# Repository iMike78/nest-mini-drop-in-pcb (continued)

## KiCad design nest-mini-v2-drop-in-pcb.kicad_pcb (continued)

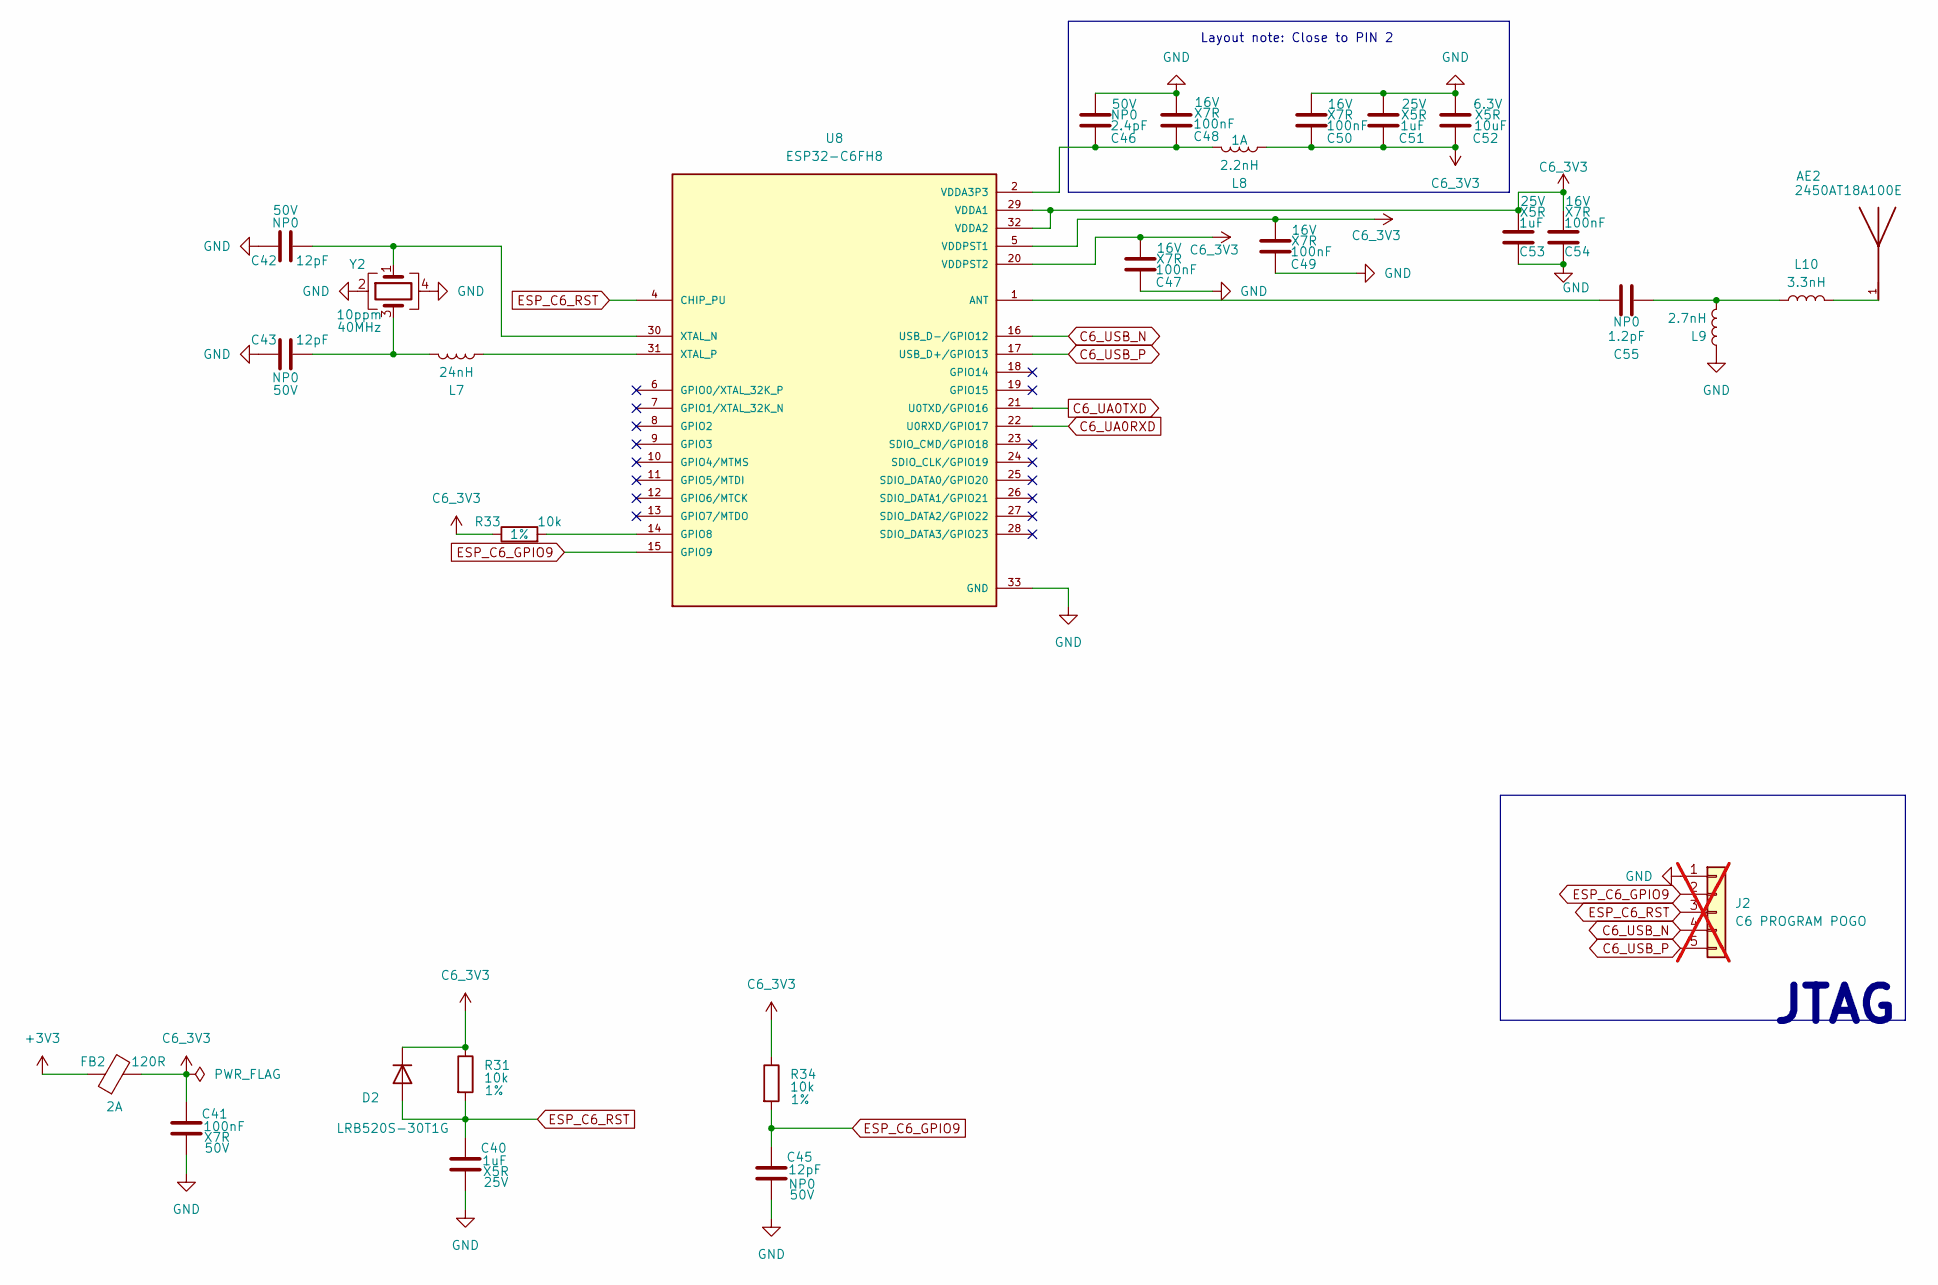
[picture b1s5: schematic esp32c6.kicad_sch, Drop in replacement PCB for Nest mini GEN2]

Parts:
AE2: 2450AT18A100E; Johanson_2450AT18x100; PARTREV 1.3; LCSC Part # C89334
C40, C51, C53: 1uF; C_0402_1005Metric; Voltage 25V; Manufacturer Part CL05A105KA5NQNC; LCSC Part # C52923
C41: 100nF; C_0603_1608Metric; Voltage 50V; Manufacturer Part CC0603KRX7R9BB104; LCSC Part # C14663
C42, C43, C45: 12pF; C_0402_1005Metric; Voltage 50V; Manufacturer Part 0402CG120J500NT; LCSC Part # C1547
C46: 2.4pF; C_0402_1005Metric; Voltage 50V; Manufacturer Part 0402CG2R4C500NT; LCSC Part # C48346
C47, C48, C49, C50, C54: 100nF; C_0402_1005Metric; Voltage 16V; Manufacturer Part CL05B104KO5NNNC; LCSC Part # C1525
C52: 10uF; C_0402_1005Metric; Voltage 6.3V; Manufacturer Part CL05A106MQ5NUNC; LCSC Part # C15525
C55: 1.2pF; C_0402_1005Metric; Voltage 50V; Manufacturer Part CC0402BRNPO9BN1R2; LCSC Part # C327292
D2: LRB520S-30T1G; D_SOD-523; Manufacturer Part LRB520S-30T1G; LCSC Part # C83680
FB2: 120R; BLM18PG121SN1D; Part number BLM18PG121SN1D; LCSC Part # C14709
J2: C6 PROGRAM POGO; PinHeader_1x05_P2.54mm_Vertical; not fitted
L7: 24nH; L_0402_1005Metric; Manufacturer Part LQW15AN24NJ00D; LCSC Part # C341784
L8: 2.2nH; L_0402_1005Metric; Manufacturer Part LQG15HS2N2B02D; LCSC Part # C162540
L9: 2.7nH; L_0402_1005Metric; Manufacturer Part MHQ1005P2N7BT000; LCSC Part # C434826
L10: 3.3nH; L_0402_1005Metric; Manufacturer Part SDCL1005C3N3STDF; LCSC Part # C16526
R31, R33, R34: 10k; R_0402_1005Metric; Tolerance 1%; Manufacturer Part 0402WGF1002TCE; LCSC Part # C25744
U8: ESP32-C6FH8; ESP32-C6FH4; Manufacturer Part ESP32-C6FH8
Y2: 40MHz; Crystal_SMD_2016-4Pin_2.0x1.6mm; Tolerance 10ppm; Manufacturer Part XRCGB40M000F1S1BR0; LCSC Part # C1870451

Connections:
+3V3: FB2.1; also elsewhere on the board
C6_3V3: C41.1, C47.2, C49.2, C50.1, C51.1, C52.1, C53.2, C54.2, D2.1 (K), FB2.2, L8.2, R31.1, R33.1, R34.1, U8.5 (VDDPST1), U8.20 (VDDPST2), U8.29 (VDDA1), U8.32 (VDDA2)
C6_UA0RXD: U8.22 (U0RXD/GPIO17); also elsewhere on the board
C6_UA0TXD: U8.21 (U0TXD/GPIO16); also elsewhere on the board
C6_USB_N: J2.4, U8.16 (USB_D-/GPIO12)
C6_USB_P: J2.5, U8.17 (USB_D+/GPIO13)
ESP_C6_GPIO9: C45.1, J2.2, R34.2, U8.15 (GPIO9); also elsewhere on the board
ESP_C6_RST: C40.1, D2.2 (A), J2.3, R31.2, U8.4 (CHIP_PU); also elsewhere on the board
GND: C40.2, C41.2, C42.1, C43.1, C45.2, C46.2, C47.1, C48.2, C49.1, C50.2, C51.2, C52.2, C53.1, C54.1, J2.1, L9.1, U8.33 (GND), Y2.2, Y2.4; also elsewhere on the board
unnamed: AE2.1, L10.2
unnamed: C43.2, L7.2, Y2.3
unnamed: C55.1, L9.2, L10.1
unnamed: C55.2, U8.1 (ANT)
unnamed: R33.2, U8.14 (GPIO8)
unnamed: C42.2, U8.30 (XTAL_N), Y2.1
unnamed: L7.1, U8.31 (XTAL_P)
VDDA3P3: C46.1, C48.1, L8.1, U8.2 (VDDA3P3), U8.3 (VDDA3P3)

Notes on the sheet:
Layout note: Close to PIN 2
JTAG

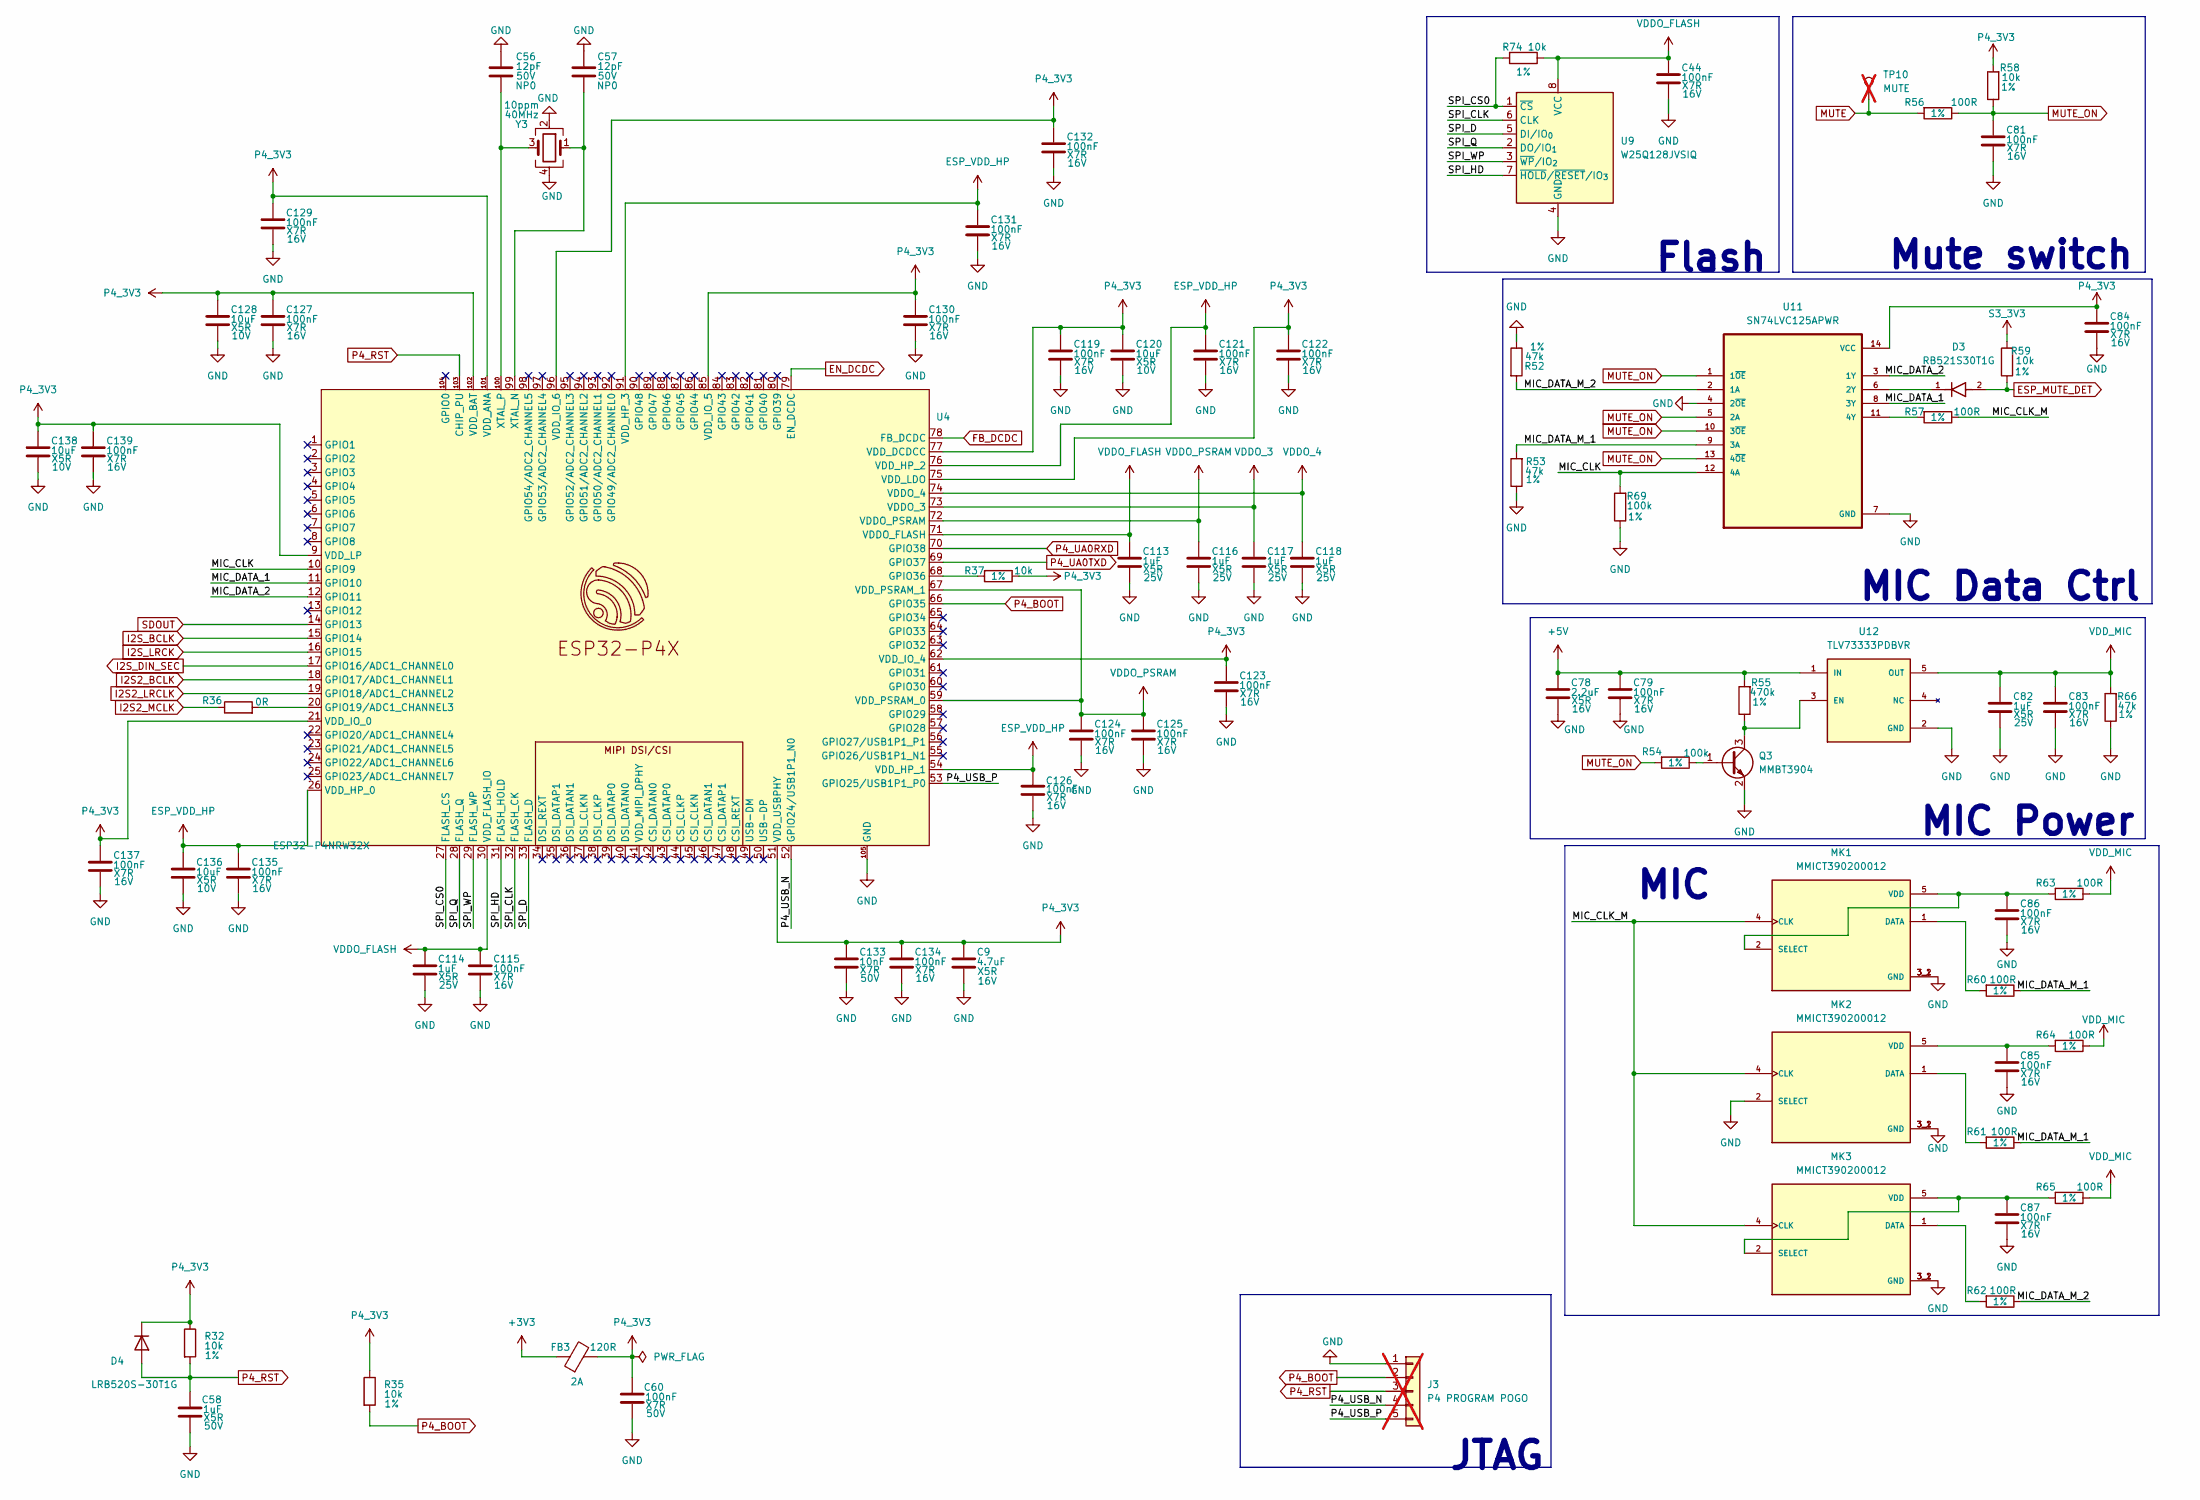
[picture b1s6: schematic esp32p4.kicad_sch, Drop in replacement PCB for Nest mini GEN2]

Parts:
C9: 4.7uF; C_0603_1608Metric; Voltage 16V; Manufacturer Part CL10A475KO8NNNC; LCSC Part # C19666
C44, C79, C81, C83, C84, C85, C86, C87, C115, C119, C121, C122, C123, C124, C125, C126, C127, C129, C130, C131, C132, C134, C135, C137, C139: 100nF; C_0402_1005Metric; Voltage 16V; Manufacturer Part CL05B104KO5NNNC; LCSC Part # C1525
C56, C57: 12pF; C_0402_1005Metric; Voltage 50V; Manufacturer Part 0402CG120J500NT; LCSC Part # C1547
C58: 1uF; C_0603_1608Metric; Voltage 50V; Manufacturer Part CL10A105KB8NNNC; LCSC Part # C15849
C60: 100nF; C_0603_1608Metric; Voltage 50V; Manufacturer Part CC0603KRX7R9BB104; LCSC Part # C14663
C78: 2.2uF; C_0603_1608Metric; Voltage 16V; Manufacturer Part CL10A225KO8NNNC; LCSC Part # C23630
C82, C113, C114, C116, C117, C118: 1uF; C_0402_1005Metric; Voltage 25V; Manufacturer Part CL05A105KA5NQNC; LCSC Part # C52923
C120, C128, C136, C138: 10uF; C_0603_1608Metric; Voltage 10V; Manufacturer Part CL10A106KP8NNNC; LCSC Part # C19702
C133: 10nF; C_0402_1005Metric; Voltage 50V; Manufacturer Part CL05B103KB5NNNC; LCSC Part # C15195
D3: RB521S30T1G; DIOM168X70N; PARTREV 7/11/1905; LCSC Part # C27636108
D4: LRB520S-30T1G; D_SOD-523; Manufacturer Part LRB520S-30T1G; LCSC Part # C83680
FB3: 120R; BLM18PG121SN1D; Part number BLM18PG121SN1D; LCSC Part # C14709
J3: P4 PROGRAM POGO; PinHeader_1x05_P2.54mm_Vertical; not fitted
MK1, MK2, MK3: MMICT390200012; MIC_T3902; PARTREV 1.0; LCSC Part # C3171752
Q3: MMBT3904; SOT-23; Manufacturer Part MMBT3904; LCSC Part # C20526
R32, R35, R37, R58, R59, R74: 10k; R_0402_1005Metric; Tolerance 1%; Manufacturer Part 0402WGF1002TCE; LCSC Part # C25744
R36: 0R; R_0402_1005Metric; Tolerance 5%; Manufacturer Part 0402WGF0000TCE; LCSC Part # C17168
R52, R53, R66: 47k; R_0402_1005Metric; Tolerance 1%; Manufacturer Part 0402WGF4702TCE; LCSC Part # C25792
R54, R69: 100k; R_0402_1005Metric; Tolerance 1%; Manufacturer Part 0402WGF1003TCE; LCSC Part # C25741
R55: 470k; R_0402_1005Metric; Tolerance 1%; Manufacturer Part 0402WGF4703TCE; LCSC Part # C25790
R56, R57, R60, R61, R62, R63, R64, R65: 100R; R_0402_1005Metric; Tolerance 1%; Manufacturer Part 0402WGF1000TCE; LCSC Part # C25076
TP10: MUTE; TestPoint_Pad_D1.0mm; not fitted
U4: ESP32-P4NRW32X; ESP32-P4; Manufacturer Part ESP32-P4NRW32X; LCSC Part # C54540373
U9: W25Q128JVSIQ; SOIC-8_5.3x5.3mm_P1.27mm; Manufacturer Part W25Q128JVSIQ; LCSC Part # C97521
U11: SN74LVC125APWR; SOP65P640X120-14N; Manufacturer Part SN74LVC125APWR; LCSC Part # C7813
U12: TLV73333PDBVR; PARTREV C; LCSC Part # C134139
Y3: 40MHz; Crystal_SMD_2016-4Pin_2.0x1.6mm; Tolerance 10ppm; Manufacturer Part XRCGB40M000F1S1BR0; LCSC Part # C1870451

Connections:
+3V3: FB3.1; also elsewhere on the board
+5V: C78.1, C79.1, R55.2, U12.1 (IN); also elsewhere on the board
/ESP32-P4/MIC_CLK: R69.2, U4.10 (GPIO9), U11.12 (4A)
/ESP32-P4/MIC_CLK_M: MK1.4 (CLK), MK2.4 (CLK), MK3.4 (CLK), R57.1
/ESP32-P4/MIC_DATA_1: U4.11 (GPIO10), U11.8 (3Y)
/ESP32-P4/MIC_DATA_2: U4.12 (GPIO11), U11.3 (1Y)
/ESP32-P4/MIC_DATA_M_1: R53.2, R60.1, R61.1, U11.9 (3A)
/ESP32-P4/MIC_DATA_M_2: R52.2, R62.1, U11.2 (1A)
/ESP32-P4/P4_USB_N: J3.4, U4.52 (GPIO24/USB1P1_N0)
/ESP32-P4/P4_USB_P: J3.5, U4.53 (GPIO25/USB1P1_P0)
/ESP32-P4/SPI_CLK: U4.32 (FLASH_CK), U9.6 (CLK)
/ESP32-P4/SPI_CS0: R74.2, U4.27 (FLASH_CS), U9.1 (~CS)
/ESP32-P4/SPI_D: U4.33 (FLASH_D), U9.5 (DI/IO_{0})
/ESP32-P4/SPI_HD: U4.31 (FLASH_HOLD), U9.7 (~HOLD/~RESET/IO_{3})
/ESP32-P4/SPI_Q: U4.28 (FLASH_Q), U9.2 (DO/IO_{1})
/ESP32-P4/SPI_WP: U4.29 (FLASH_WP), U9.3 (~WP/IO_{2})
EN_DCDC: U4.79 (EN_DCDC); also elsewhere on the board
ESP_MUTE_DET: D3.2, R59.1; also elsewhere on the board
ESP_VDD_HP: C121.1, C126.1, C131.1, C135.1, C136.1, U4.26 (VDD_HP_0), U4.54 (VDD_HP_1), U4.76 (VDD_HP_2), U4.91 (VDD_HP_3); also elsewhere on the board
FB_DCDC: U4.78 (FB_DCDC); also elsewhere on the board
GND: C9.2, C44.2, C56.1, C57.1, C58.2, C60.2, C78.2, C79.2, C81.2, C82.2, C83.2, C84.2, C85.2, C86.2, C87.2, C113.2, C114.2, C115.2, C116.2, C117.2, C118.2, C119.2, C120.2, C121.2, C122.2, C123.2, C124.2, C125.2, C126.2, C127.2, C128.2, C129.2, C130.2, C131.2, C132.2, C133.2, C134.2, C135.2, C136.2, C137.2, C138.2, C139.2, J3.1, MK1.3_1 (GND), MK1.3_2 (GND), MK2.2 (SELECT), MK2.3_1 (GND), MK2.3_2 (GND), MK3.3_1 (GND), MK3.3_2 (GND), Q3.2 (E), R52.1, R53.1, R66.1, R69.1, U4.105 (GND), U9.4 (GND), U11.4 (2~OE), U11.7 (GND), U12.2 (GND), Y3.2, Y3.4; also elsewhere on the board
I2S2_BCLK: U4.18 (GPIO17/ADC1_CHANNEL1); also elsewhere on the board
I2S2_LRCLK: U4.19 (GPIO18/ADC1_CHANNEL2); also elsewhere on the board
I2S2_MCLK: R36.1; also elsewhere on the board
I2S_BCLK: U4.15 (GPIO14); also elsewhere on the board
I2S_DIN_SEC: U4.17 (GPIO16/ADC1_CHANNEL0); also elsewhere on the board
I2S_LRCK: U4.16 (GPIO15); also elsewhere on the board
MUTE: R56.2, TP10.1 (1_1); also elsewhere on the board
MUTE_ON: C81.1, R54.2, R56.1, R58.1, U11.1 (1~OE), U11.5 (2A), U11.10 (3~OE), U11.13 (4~OE)
unnamed: MK1.1 (DATA), R60.2
unnamed: C86.1, MK1.2 (SELECT), MK1.5 (VDD), R63.2
unnamed: MK2.1 (DATA), R61.2
unnamed: C85.1, MK2.5 (VDD), R64.2
unnamed: MK3.1 (DATA), R62.2
unnamed: C87.1, MK3.2 (SELECT), MK3.5 (VDD), R65.2
unnamed: Q3.1 (B), R54.1
unnamed: Q3.3 (C), R55.1, U12.3 (EN)
unnamed: R36.2, U4.20 (GPIO19/ADC1_CHANNEL3)
unnamed: R37.2, U4.68 (GPIO36)
unnamed: C57.2, U4.99 (XTAL_N), Y3.1
unnamed: C56.2, U4.100 (XTAL_P), Y3.3
unnamed: D3.1, U11.6 (2Y)
unnamed: R57.2, U11.11 (4Y)
P4_3V3: C9.1, C60.1, C84.1, C119.1, C120.1, C122.1, C123.1, C127.1, C128.1, C129.1, C130.1, C132.1, C133.1, C134.1, C137.1, C138.1, C139.1, D4.1 (K), FB3.2, R32.1, R35.1, R37.1, R58.2, U4.9 (VDD_LP), U4.21 (VDD_IO_0), U4.51 (VDD_USBPHY), U4.62 (VDD_IO_4), U4.75 (VDD_LDO), U4.77 (VDD_DCDCC), U4.85 (VDD_IO_5), U4.96 (VDD_IO_6), U4.101 (VDD_ANA), U4.102 (VDD_BAT), U11.14 (VCC)
P4_BOOT: J3.2, R35.2, U4.66 (GPIO35); also elsewhere on the board
P4_RST: C58.1, D4.2 (A), J3.3, R32.2, U4.103 (CHIP_PU); also elsewhere on the board
P4_UA0RXD: U4.70 (GPIO38); also elsewhere on the board
P4_UA0TXD: U4.69 (GPIO37); also elsewhere on the board
S3_3V3: R59.2; also elsewhere on the board
SDOUT: U4.14 (GPIO13); also elsewhere on the board
VDDO_3: C117.1, U4.73 (VDDO_3)
VDDO_4: C118.1, U4.74 (VDDO_4)
VDDO_FLASH: C44.1, C113.1, C114.1, C115.1, R74.1, U4.30 (VDD_FLASH_IO), U4.71 (VDDO_FLASH), U9.8 (VCC)
VDDO_PSRAM: C116.1, C124.1, C125.1, U4.59 (VDD_PSRAM_0), U4.67 (VDD_PSRAM_1), U4.72 (VDDO_PSRAM)
VDD_MIC: C82.1, C83.1, R63.1, R64.1, R65.1, R66.2, U12.5 (OUT)

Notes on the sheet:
MIC
Mute switch
MIC Power
Flash
MIC Data Ctrl
JTAG

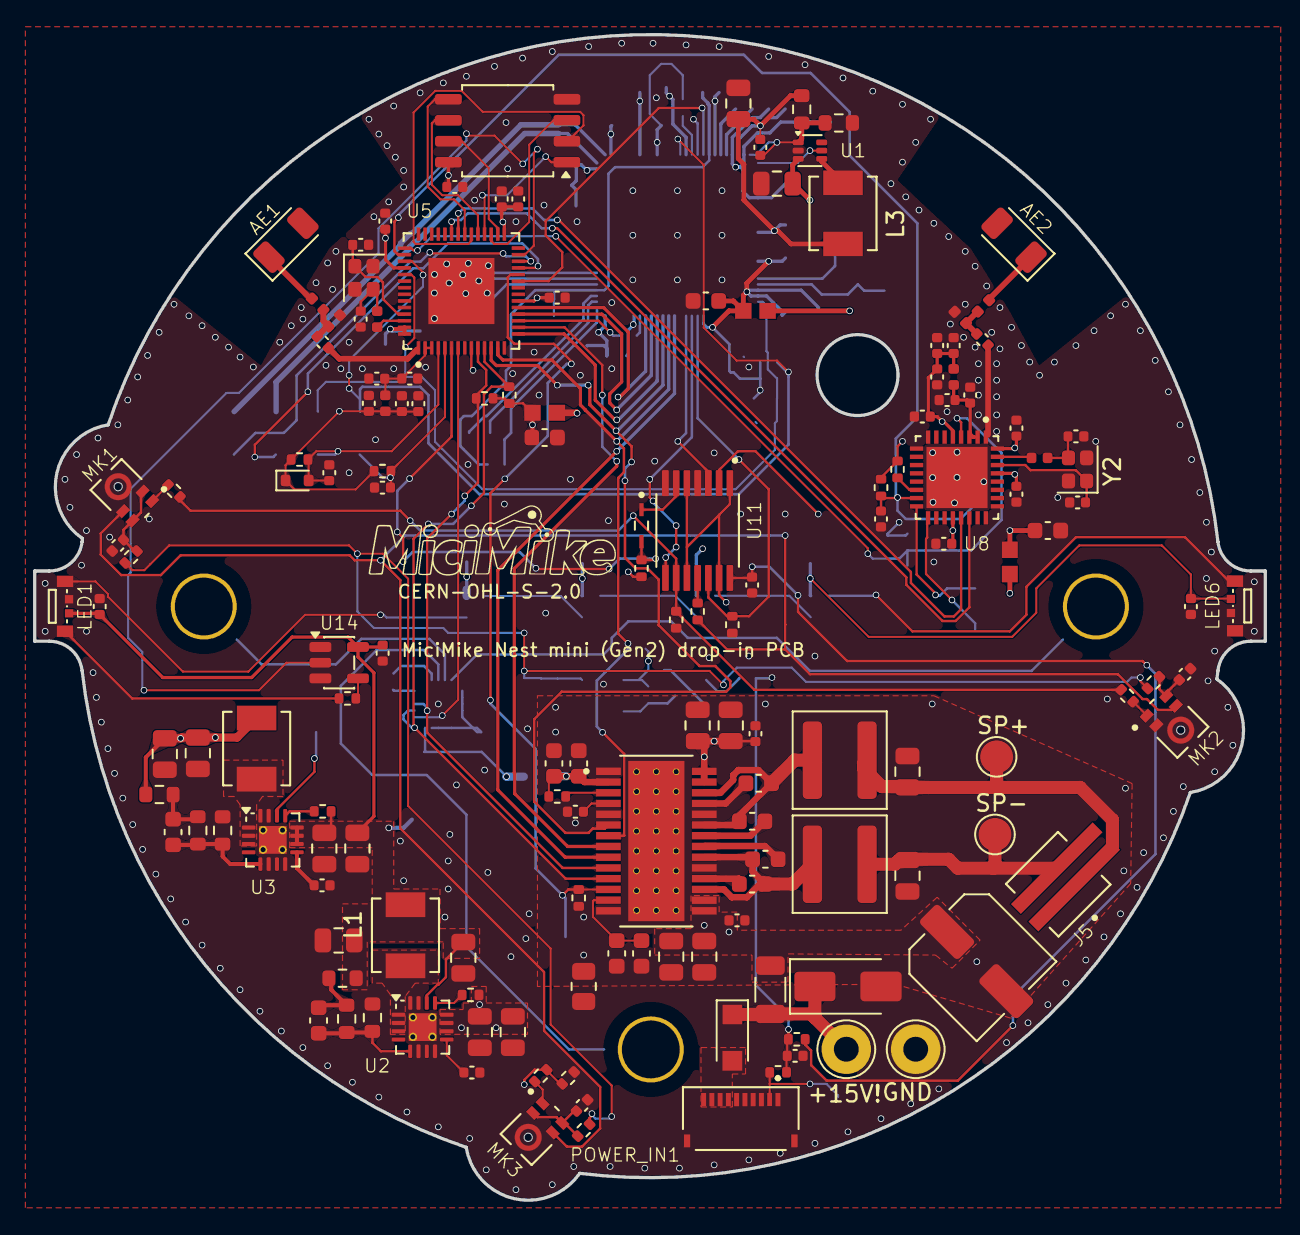
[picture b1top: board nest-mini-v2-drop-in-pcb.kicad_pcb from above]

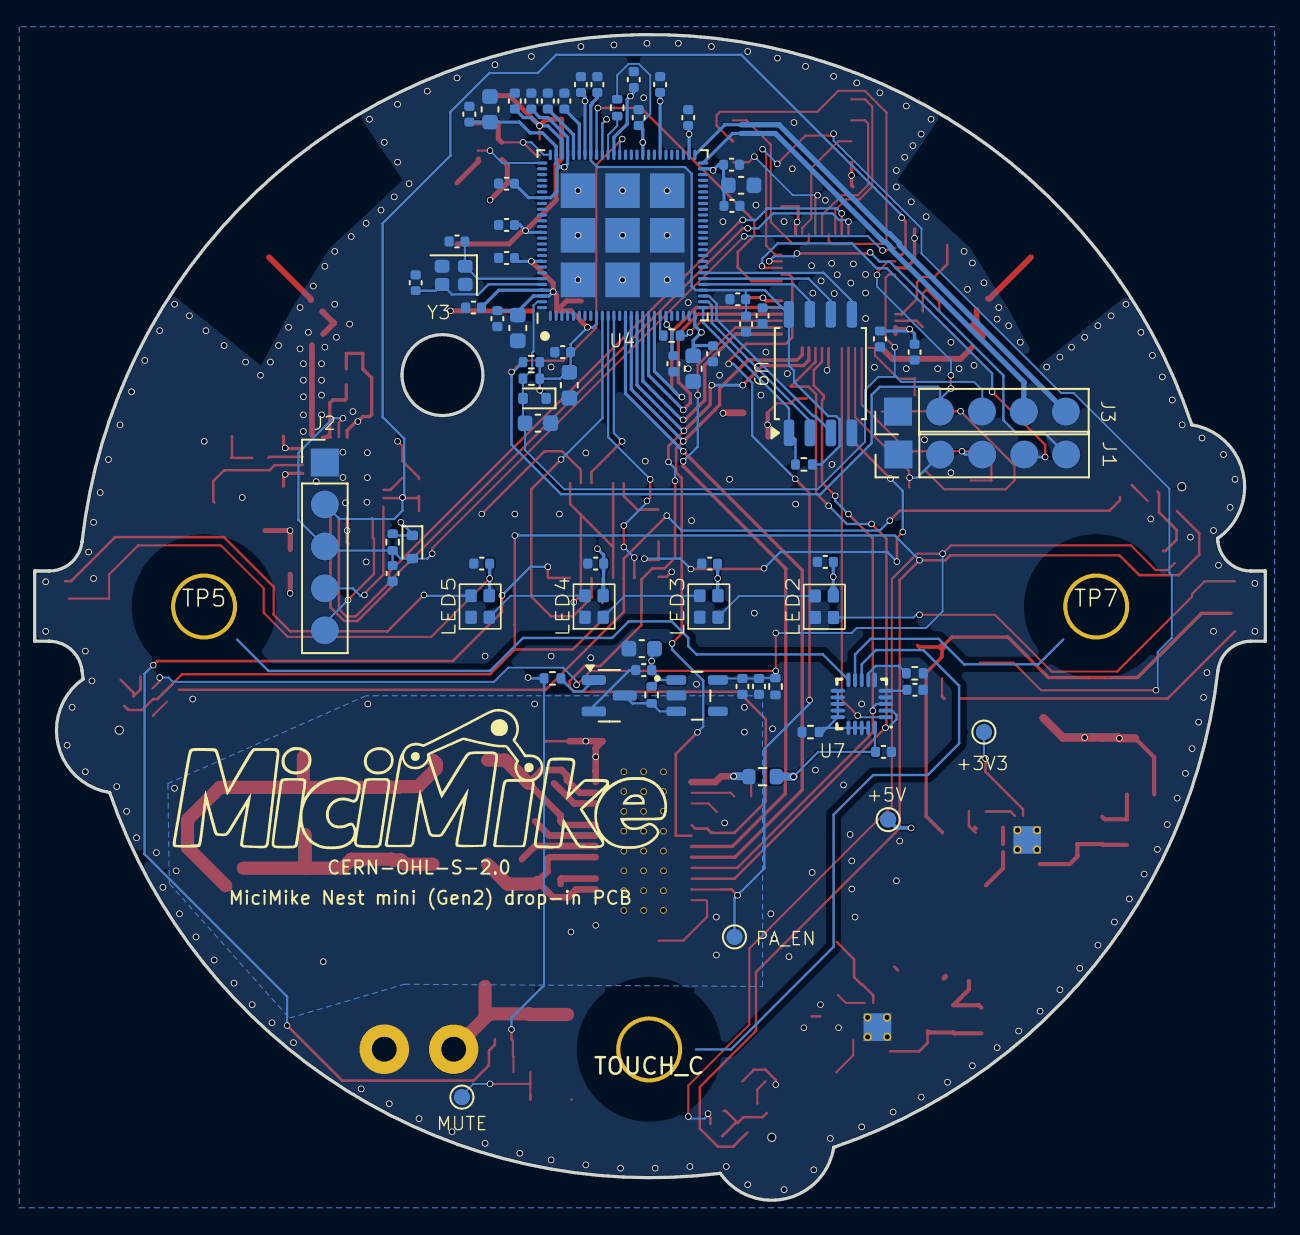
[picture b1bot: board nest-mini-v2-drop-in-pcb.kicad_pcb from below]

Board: 4 copper layers, 74.5 x 70.6 mm, 229 parts (79 on the bottom side), 133 nets.
